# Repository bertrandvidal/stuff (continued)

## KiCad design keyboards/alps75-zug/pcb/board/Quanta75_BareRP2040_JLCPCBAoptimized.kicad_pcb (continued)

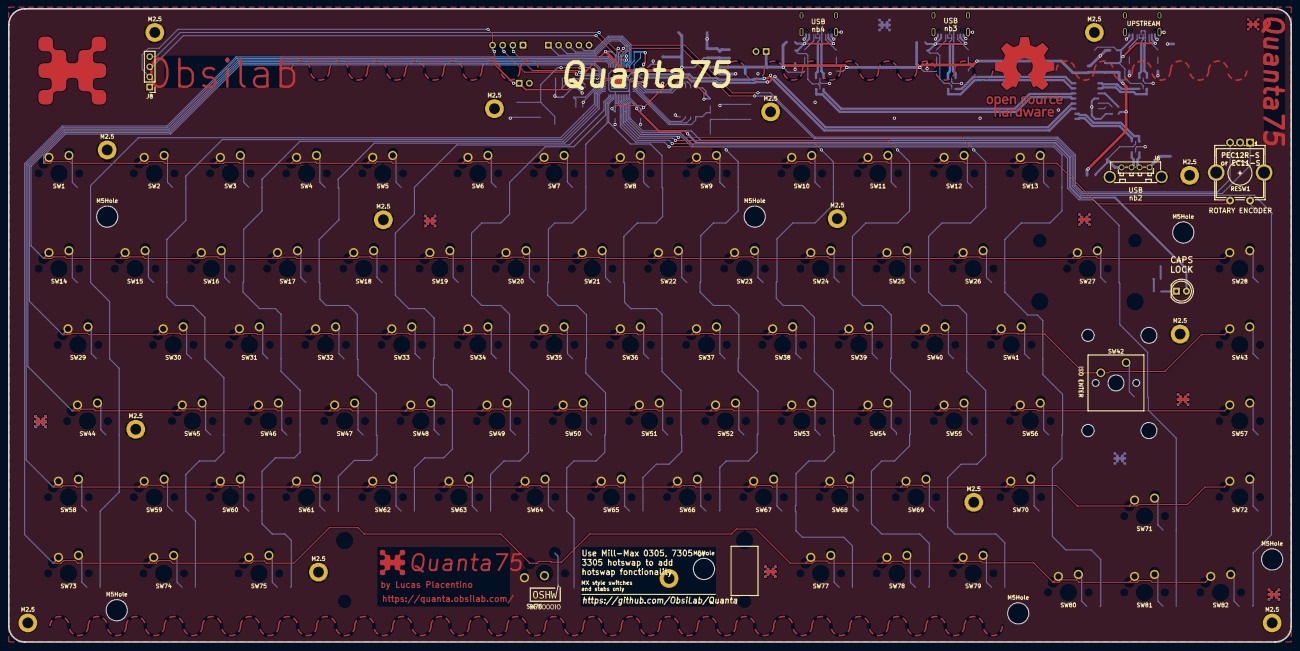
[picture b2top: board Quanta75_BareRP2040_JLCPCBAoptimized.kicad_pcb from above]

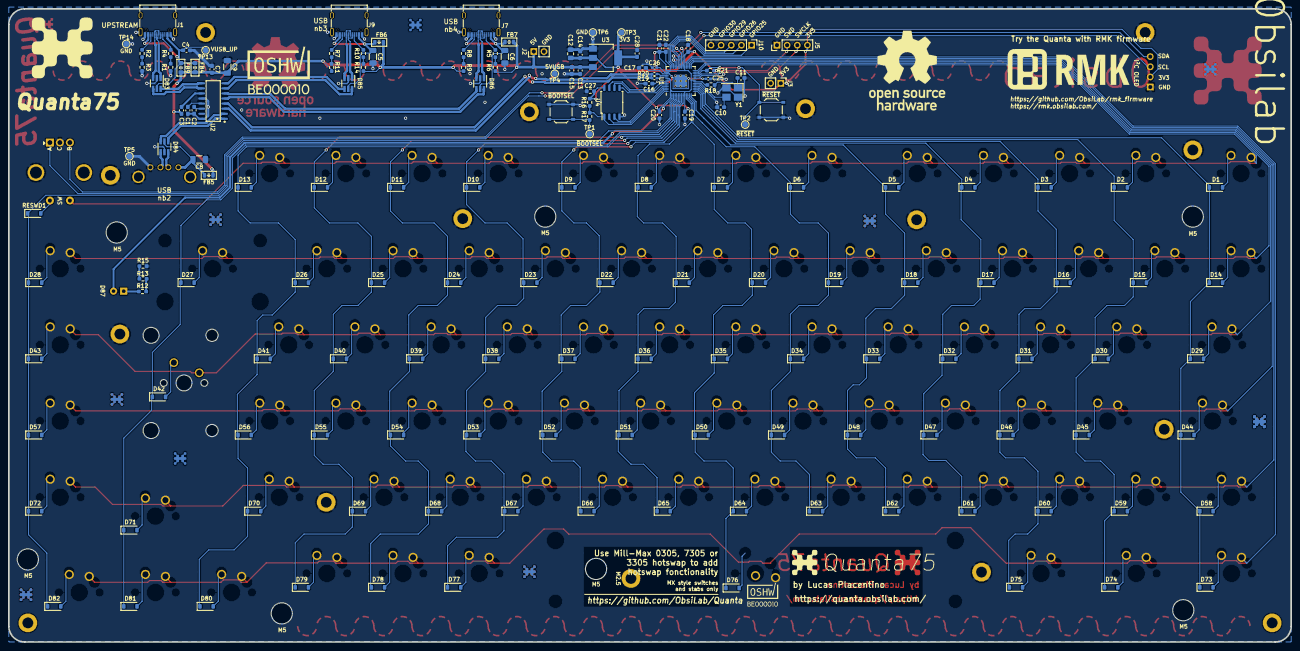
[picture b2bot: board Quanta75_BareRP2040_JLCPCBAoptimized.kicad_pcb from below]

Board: 2 copper layers, 320.7 x 158.3 mm, 269 parts (160 on the bottom side), 172 nets.

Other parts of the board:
M2.5, M2.5#2, M2.5#3, M2.5#4, M2.5#5, M2.5#6, M2.5#7, M2.5#8, M2.5#9, M2.5#10, M2.5#11, M2.5#12, M2.5#13, M2.5#14, M2.5#15: MountingHole_2.7mm_M2.5_DIN965_Pad
M5Hole, M5Hole#2, M5Hole#3, M5Hole#4, M5Hole#5, M5Hole#6, M5Hole#7: MountingHole_5.3mm_M5
OSHW-logo: OSHW-Logo_19x20mm_Copper
Quanta***: LOGO; Quanta-logo
TP5: GND; TestPoint_Pad_D1.5mm

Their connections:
GND: M2.5.1, M2.5#2.1, M2.5#4.1, M2.5#5.1, M2.5#6.1, M2.5#7.1, M2.5#8.1, M2.5#9.1, M2.5#10.1, M2.5#11.1, M2.5#12.1, M2.5#13.1, TP5.1; also elsewhere on the board

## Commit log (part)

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2014-11-21 First working draft
2014-11-21 Do not return a multiple of 60 for start and run time
    To avoid playing a finite number of minute a more "random" portion of the movie
    we return a number between 10 and 60.
    Also the get_movie method returns a list and is no longer a generator this way
    we can shuffle it.
2015-01-24 Base files for a Django tutorial project
    Tutorial taken from https://docs.djangoproject.com/en/1.7/intro/tutorial01/
2015-01-24 Add pretty print method for models
    It's always better to have the models's instances being correctly displayed
2015-01-25 Make Django Admin more user friendly
    We make the Admin panel more user friendly by having 3 extra Choices ready
    to be created when adding a Question, search and filter can be applied to the
    Question change list and we display other fields/method i.e. pub_date and
    was_published_recently
2015-01-26 Playing around with templates
    Specialize the Admin html template.
    Make the polls index page into a bullet list of the latest questions.
2015-01-26 Use namespaced urls
2015-01-26 Properly display the results of a poll
2015-01-26 Introduce simple models tests
    Fix a bug in was_published_recently
2015-01-26 Add tests for detail view
2015-01-26 Move polls application to a specific dir for packaging tuto
2015-01-26 Add license and readme files
2015-01-27 Straight forward solution
2015-07-25 [ideas]add two new ideas
2015-10-17 [ALGO]Bin search in an ordered array
    The point was to print the number of operations/calls made by a bin
    search.
2015-10-19 Are two strings permutation of each others
    Simple methods to test if two strings are permutation of each others.
    is_permutation sorts both strings and return True if the result is the
    same, False otherwise. Sorts takes O(n log n)
    array_permutation creates an array of 128 zeros to count the occurrence
    of each ASCII char in the strings. Increment the correct position in the
    array for str1 and decrement the correct position for each char of str2.
2015-10-19 In place string reverse
    Do not use the slice operator or the reversed built-in.
2015-10-19 Classical sort algo
2015-11-04 Add a Snippet model
2015-11-04 Use ModelSerializer for SnippetSerializer
2015-11-04 Plug views to URLs
2015-11-04 Fix syntax error in urls.py
2015-11-04 Add format suffixes to URLs
2015-11-04 Adapt views to use DRF generics
2015-11-04 Add serializers, views and URLs for users
2015-11-04 Add permission on snippets
2015-11-04 Add a permission so only owners can delete/edit snippets
2015-11-04 Introduce SnippetHighlight and hyperlinking
2015-11-04 Auth URLs are in snippets/urls.py
2016-04-09 4 spaces indent + print time
2016-05-14 Add counter for number of operation/node visit
    Helps understand what's going on and how those algorithms work
2016-05-14 Update link for triangle exercise
    Yodle link is disabled - use codeeval.com link instead.
2016-12-31 [JIRA] Add script to get stats from JIRA
    @CrowdTwist/t2jd
    @jtaoct @Askent @dkarten
2016-12-31 [5Q] Python test for 5q
2017-10-18 Format poultry
2017-10-18 Check for exact match of letter & counter
2017-10-18 Update md5 to include white spaces
2017-10-21 Replace test data with the real deal
2017-10-21 Add README with the url of the exercise
2017-10-21 Create a word_contains method
2019-10-22 [ANTS] Add a main 'method'
2019-10-22 [ANTS] Add a class to make things a little cleaner
2019-10-22 [ANTS] Move some more function into the class
    Yay for OOP-ish
2019-10-23 [ANTS] Make a global an attribute
2019-10-23 [ANTS] Remove unused global
2019-10-23 [ANTS] Add much needed docblock
2019-10-23 [ANTS] Rename param
2019-10-23 [ANTS] Fix non-existent var... that's the problem when your algo is too slow
2019-10-23 [ANTS] Add tests for nb_leaf_nodes and subsequentially fix the method
2019-10-23 [ANTS] Add first test for build_tree mehod
2019-10-29 [ANTS] Add tests for add_node
2019-10-29 [ANTS] Add tests for build_tree
2019-10-29 [ANTS] Add tests for find_match
2019-10-29 [ANTS] Things
2019-11-02 [ANTS] Move print tree method to main file
2019-11-02 [PvA] Create smaller input files for easier testing
2019-11-02 [PvA] Test for counter equality before checking permutation md5
2019-11-02 [PvA] something something optimization
2020-08-22 Add kbd75v2 qmk firmware file
    Firmware for kbd75v2 layout as per https://config.qmk.fm/
    Tests:
    - well I'm writing this commit message with the keyboard so I guess that
    works
2020-11-10 [ALGO] As taken from https://leetcode.com/problems/add-two-numbers/
2020-11-26 [LRU] Add cache's capacity
    This will be the maximum amount of items that can be held in the cache.
    Tests:
    - lru tests OK
2020-11-27 [LRU] Add typing & docstring
    Tests:
    - none
2020-11-27 [LRU] Prevent cache size from going over capacity
    If any key is being added that would bring the cache size beyond the
    capacity the least recently used key is evicted.
    We maintain an in order "access log" for keys so that the latest key
    added or accessed will always be the head of that log. The least
    recently access entry is last and is popped out whenever the addition of
    a key would result in going over the set capacity.
2020-11-27 [LRU] Add docstring
2020-12-09 [Triangle] Update link to excercise
    Update link to exercise to the one I use during interview
2021-01-16 [AUDIO-IMG] Calculate min/max pixel for each column
2021-01-16 [AUDIO-IMG] Change wave range to 16-bit
2021-01-16 [AUDIO-IMG] (0,0) is upper left so min is max and max is min!
    2 things:
    1/ I should have know that the origin is upper left
    2/ It's mentioned in the video that at some point max_val = min(...)
    :facepalm-hard:
    What we see as the max (the highest non black pixel) is the closest to
    the top of the image (i.e. lower values of the y-axis) so taking the min
2021-01-16 [AUDIO-IMG] Gradually go from one avg to the next
    We take the middle between the image's min/max non black pixel (albeit
    reversed because upper left == (0, 0)) and gradually "link" it in a
    straight line with the previous average
    Oh yeah I forgot ... that still don't work!
2021-01-16 [AUDIO-IMG] Really convert to black an white
2021-01-16 [AUDIO-IMG] Remove wav creation since it's not working
2021-01-16 [AUDIO-IMG] More eye debugging
    Draw the "avg" pixel with BLUE aaaaaand they're wrong
2021-01-16 [AUDIO-IMG] Scale value for debuggin
2021-01-16 [AUDIO-IMG] Obtain scaled up viz of what the wave file will look like
    That one took some freaking time...
    We obtain a final image with min/max/avg/interpolation for scaled up
    image
2021-01-16 [AUDIO-IMG] Rename vars for readability
2021-01-16 [AUDIO-IMG] Remove unnecessary assertion
2021-01-16 [AUDIO-IMG] Generate wav file ... it's garbage :)
2021-01-21 [AUDIO-IMG] Formatting
2021-01-21 [AUDIO-IMG] Move stuff around
2021-01-21 [AUDIO-IMG] It's wav not wave Bert
2021-01-21 [AUDIO-IMG] Play around with wav params
2021-01-21 [AUDIO-IMG] Leave a message for my future self
2021-01-23 [AUDIO-IMG] Rename output files to be ordered
2021-01-23 [AUDIO-IMG] Move methods to top of file
2021-01-23 [AUDIO-IMG] Ignore X-axis
2021-01-23 [AUDIO-IMG] Remove poor testing data
    The sample was too long/the image didn't have enough detail to be able
    to reconstruct from it.
    It has been decided to remove it!
    Tests:
    - success was had with the yes.png testin data
2021-01-23 [AUDIO-IMG] Add more testing data
2021-01-23 [AUDIO-IMG] Skip a few pixels at top & bottom for noise
2021-01-23 [AUDIO-IMG] Add todos you know for later ...
2021-02-07 [AUDIO-IMG] Attempt to fit wav values using polynomial function
    We use numpy to fit the values with a polynomial function.
    Unsuccessfully... for now...
    The length of the debug image and wav file are very very small ...
    unclear why
2021-02-27 [CFART] Use underscores Luke
2021-02-27 [CFART] Formatting
2021-02-27 [CFART] Add Grammar Class
2021-02-27 [CFART] Add number of sequences to generate
2021-02-27 [CFART] No Dupes Allowed
2021-02-28 [CFART] WIP
2021-02-28 [CFART] Make Display return their dimension
2021-02-28 [CFART] Rename vars
2021-02-28 [CFART] Add space when display for better effect:
2021-02-28 [CFART] Add a 'complete' test to facilitate ... well testing
2021-04-03 [CFART] Remove space when display to terminal
2021-04-03 [CFART] Add skeleton for an Image Canvas
2021-04-03 [CFART] Implement and test RgbImage.dimension
2021-04-03 [CFART] Grammar are really a set of Rules
2021-04-03 [CFART] Add test for Canvas.contains
2021-04-03 [CFART] Add LambdaRule for best of both worlds
2021-04-05 [CFART] WIP something is off - to be investigated
2021-05-09 [PIXELS] Add enum for pixel colors
    Tests:
    - none
2021-05-09 [PIXELS] Add a simple Pixel class
    For now Pixel is a simple data object, also add some simplistic tests.
    Tests:
    - PixelTest OK
2021-05-09 [PIXELS] Add method to check is a Chamber is empty
    This will be useful to iterate until all pixels are out of the Chamber
    Tests:
    - ChamberTest OK
2021-05-09 [PIXELS] Define how color impacts movement of Pixel
    Each color "makes" pixels move in a certain direction.
    This translate to applying a transformation to the Pixel's position
    Tests:
    - ColorTest OK
2021-05-09 [PIXELS] Add method Chamber::movePixels
    The Chamber will move the pixels according to their color, if they are
    out of bound they are removed.
    Tests:
    - ChamberTest OK
2021-05-09 [PIXELS] Add Pixel::move
    Pixel update their position when moving. The computation is left to
    their Color since it is what govern the direction.
    Tests:
    - PixelTest OK
2021-05-09 [PIXELS] Add Chamber::getSize
    Tests:
    - none
2021-05-09 [PIXELS] Implement representing a Chamber as test
    The method allows us to translate the state of a Chamber to a String.
    Tests:
    - TextVisualizationTest OK
2021-05-09 [PIXELS] Add original state to output
    This will help show where we started from.
    Tests:
    - tested using cli directly
2021-05-09 [PIXELS] Update javadoc
2021-05-09 [PIXELS] Use Color.getMovement method
    Using the getMovement method reads better
    Tests:
    - PixelTest OK
2021-05-09 [PIXELS] Rework visualization to not have to rely on Color being one lettered
    It's not great that we need our Colors to be one lettered just to use
    "Enum:valueOf". Make modification so that we don't rely on this
    method.
    Tests:
    - ./gradlew test OK
2021-05-09 [PIXELS] Add TODOs for future improvements
2021-06-12 [PIXELS] Code cleanup
2021-06-12 [PIXEL] Do not test for ordering
    Testing for equality on list takes order into account. We instead test
    that one list contains all the elements from the other.
    Tests:
    - ./gradlew test --rerun-tasks
2021-06-12 [PIXEL] Make blank character a constant
    Rather than having '.' hardcoded in several places we create a constant
    that TextVisualization defines as the "empty space" in a textual
    chamber.
    Tests:
    - ./gradlew test --rerun-tasks
2021-06-12 [PIXELS] Leverage new Color.pixelAt method
2021-06-12 [PIXELS] Orange input pixels are not a special case anymore
    Now that we created the ORANGE color it can behave the same way as any
    other color and when that color is found we can "create" the pixels at
    the given position.
    Tests:
    - ./gradlew test
2021-06-27 [KBORAD] Switch DEL/backlight toggle
2021-06-27 [KBOARD] Update layout for kbd75
2021-09-19 [KBOARD] add json layout file for YMDK split 75%
2021-10-23 [BK] Add my current list of worthy-read bookmarks
2021-10-23 [BK] Classify my bookmarks based on topic using textrazor.com
2021-10-24 [BK] Refactor to pick up where we left off
2021-10-24 [BK] Use constant
2021-10-24 [BK] Update typing to match actual object
2021-10-24 [BK] Return set of links to speed up 'in' operation
2021-10-24 [BK] Transform bookmarks to HTML
2021-11-05 [TRIANGLE] Terrible in Java
2021-12-12 [KEEBS] Add layout for kbd75hs
2022-07-03 Good ol' off-by-one error in prison riddle
    random.randint is [a, b] while range(a, b) is [a, b[ so if nb_user = b
    we end up with out of range index
2023-07-02 Add empty files
2023-07-02 Handle zipped and unzipped files
2023-07-02 Find thermostat attribute in a file
2023-07-03 Parse CLI args and print output
